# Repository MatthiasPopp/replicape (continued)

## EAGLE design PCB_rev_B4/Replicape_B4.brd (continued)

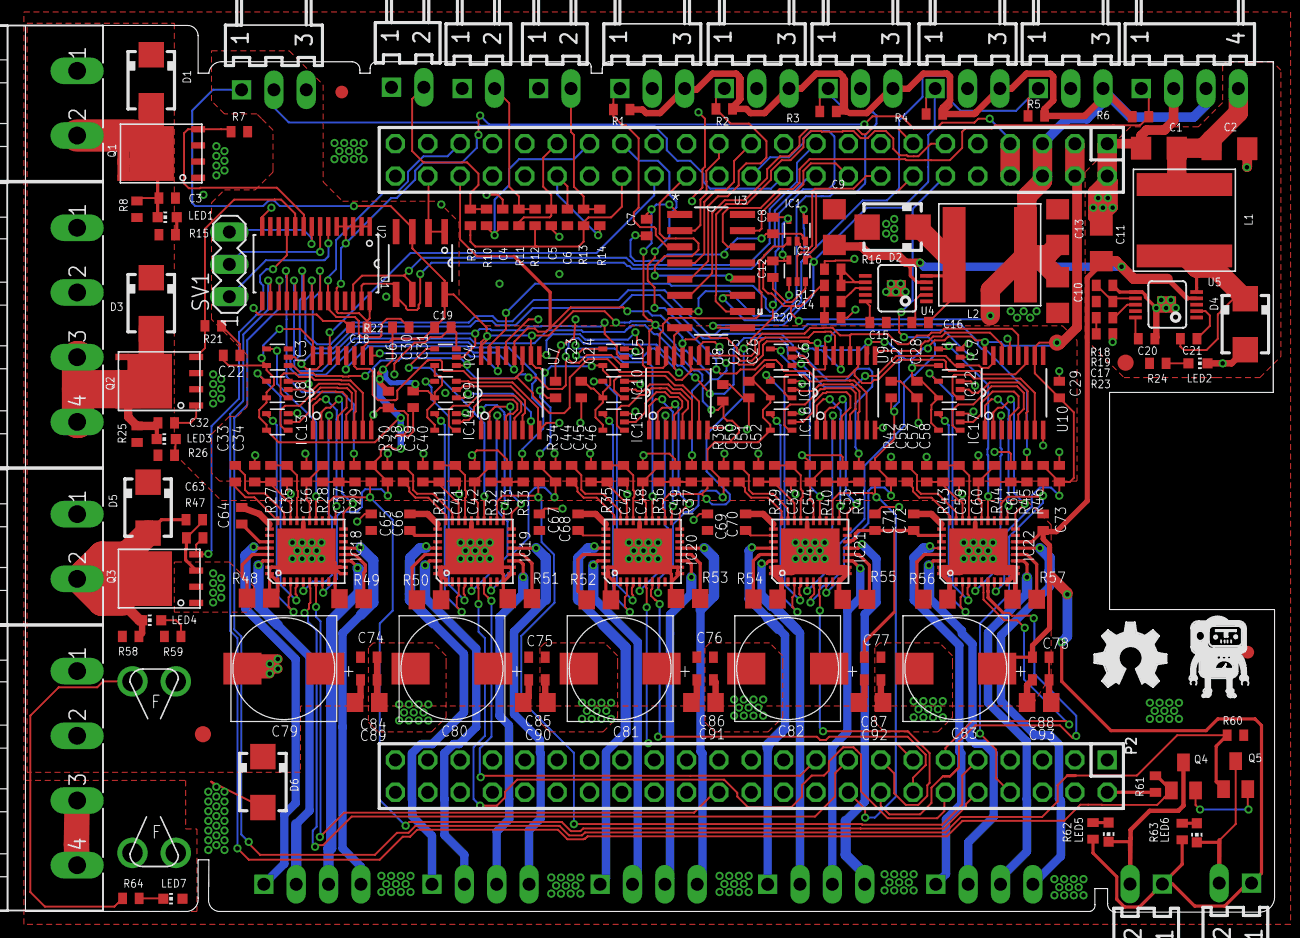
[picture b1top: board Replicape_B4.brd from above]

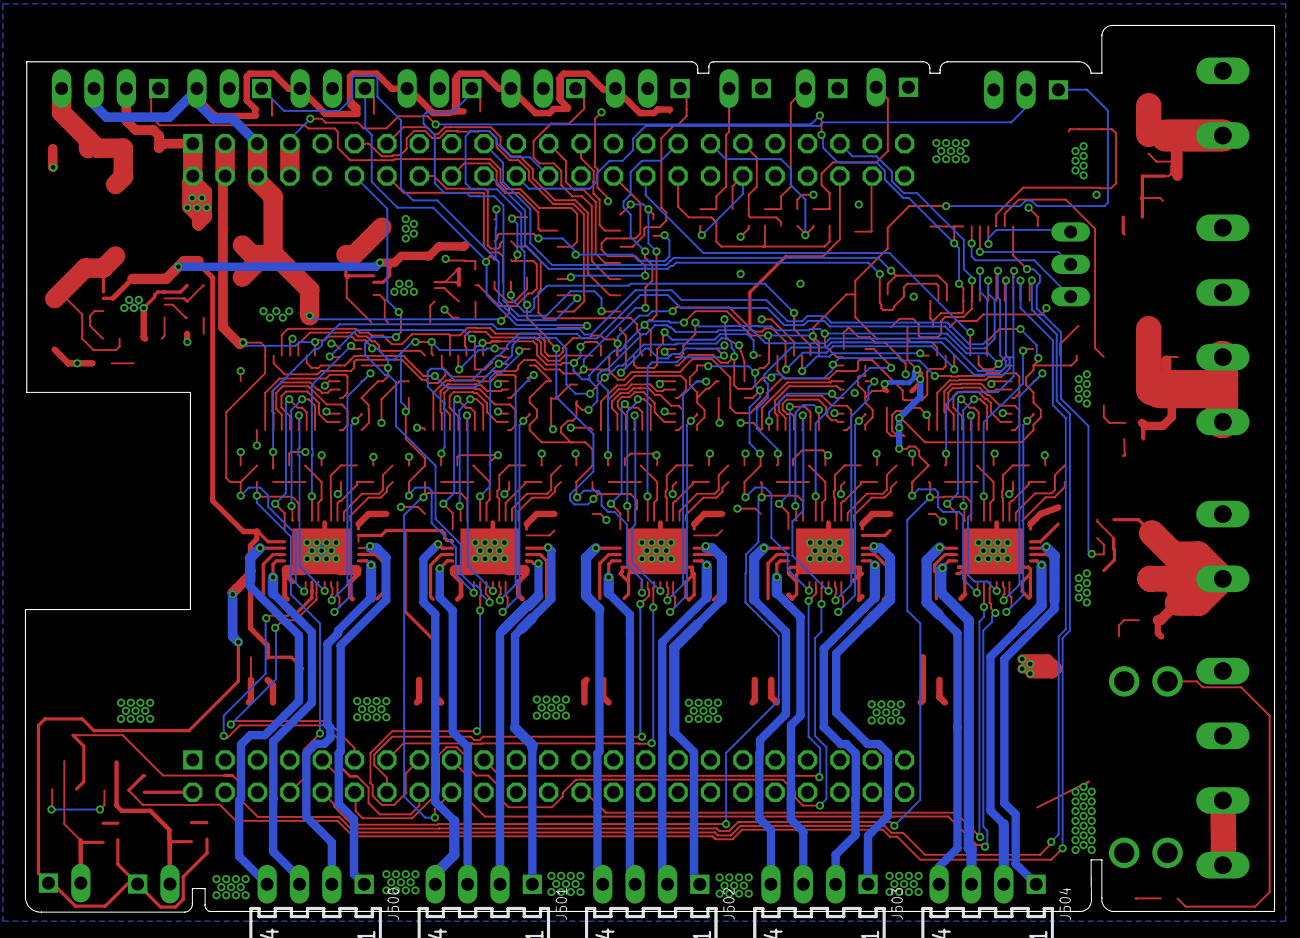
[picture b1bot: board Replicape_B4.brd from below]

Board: 2 copper layers, 98.1 x 69.6 mm, 249 parts (5 on the bottom side), 211 nets.

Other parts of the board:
U$2: LOGO_BIG

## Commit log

2019-10-06 changed the b4 version from 4 layer to 2 layer pcb and removed drc failures
